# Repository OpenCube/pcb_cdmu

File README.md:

OpenCube CDMU
=============

The OpenCube Command and Data Management Unit (CDMU) is an embedded Linux computer. It coordinates the various functions of the spacecraft. In particular, it peforms the following tasks:

 * Telemetry pre-processing and encoding
 * Telecommand decoding
 * Communication session management
 * Resource allocation
 * Fault mitigation

In its current version, it consists of a BeagleBone Black board mounted on a custom circuit board with CAN bus transceivers. In the future, the board will also include a latch-up protection circuit, external memory (FRAM) and an external watchdog circuit. Eventually, the BeagleBone will be replaced with an AM3359 processor and its support components.

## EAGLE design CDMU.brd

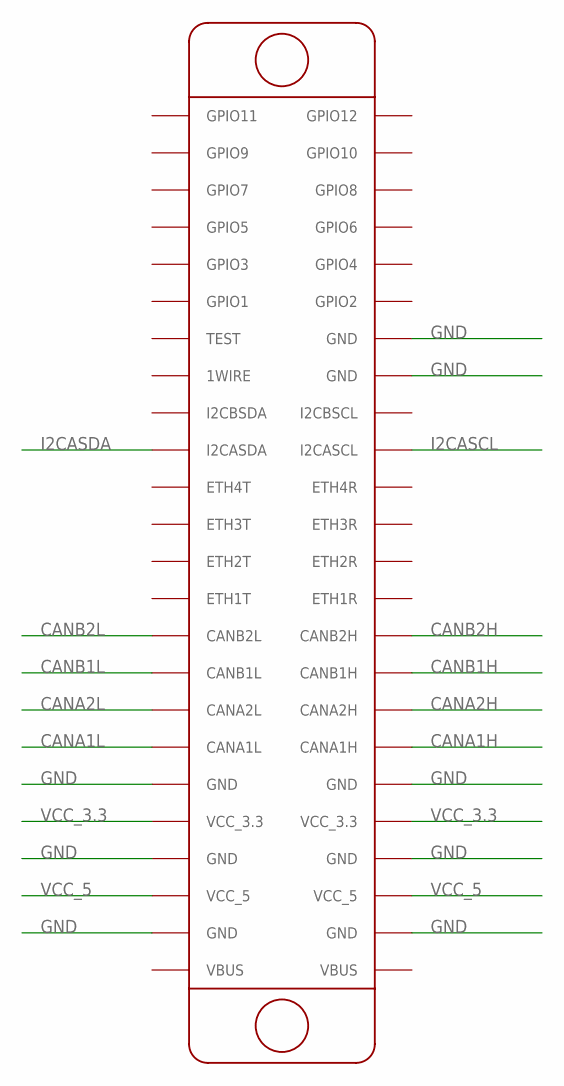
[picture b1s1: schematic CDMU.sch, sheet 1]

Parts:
U$1: CUBESAT_PCB

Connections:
CANA1H: U$1.CANA1H; also elsewhere on the board
CANA1L: U$1.CANA1L; also elsewhere on the board
CANA2H: U$1.CANA2H; also elsewhere on the board
CANA2L: U$1.CANA2L; also elsewhere on the board
CANB1H: U$1.CANB1H; also elsewhere on the board
CANB1L: U$1.CANB1L; also elsewhere on the board
CANB2H: U$1.CANB2H; also elsewhere on the board
CANB2L: U$1.CANB2L; also elsewhere on the board
GND: U$1.GND@5 (GND), U$1.GND@6 (GND), U$1.GND@7 (GND), U$1.GND@8 (GND), U$1.GND@9 (GND), U$1.GND@10 (GND), U$1.GND@11 (GND), U$1.GND@12 (GND); also elsewhere on the board
I2CASCL: U$1.I2CASCL; also elsewhere on the board
I2CASDA: U$1.I2CASDA; also elsewhere on the board
VCC_3.3: U$1.VCC_3.3@1 (VCC_3.3), U$1.VCC_3.3@2 (VCC_3.3); also elsewhere on the board
VCC_5: U$1.VCC_5@1 (VCC_5), U$1.VCC_5@2 (VCC_5); also elsewhere on the board

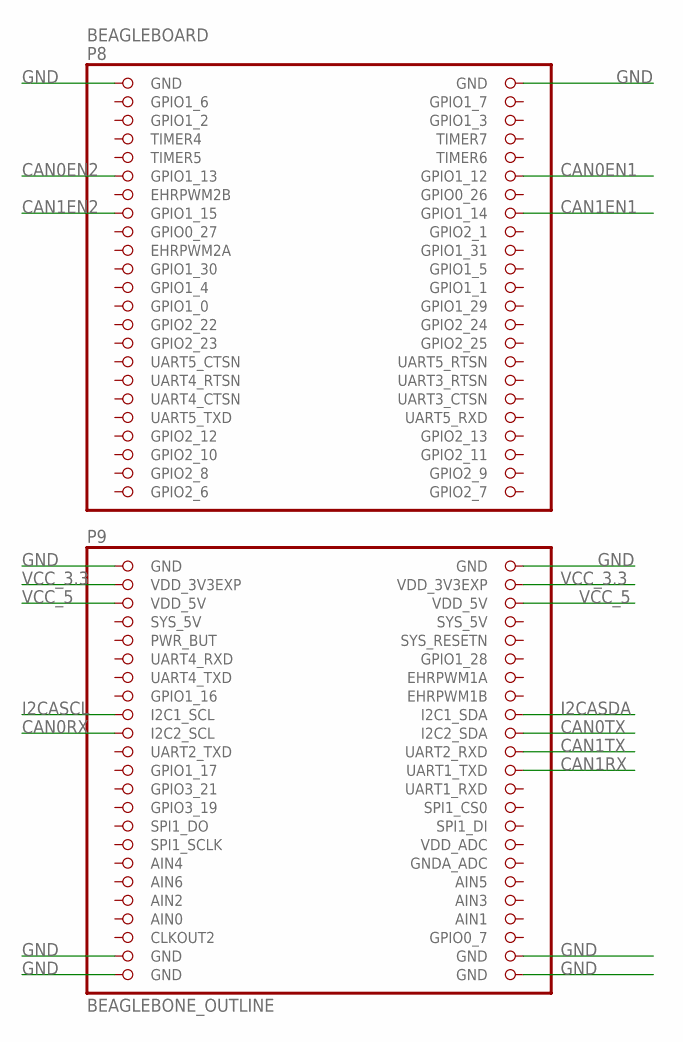
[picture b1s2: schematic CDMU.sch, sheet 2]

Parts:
BEAGLEBOARD: BEAGLEBONE_OUTLINE; BEAGLEBONE_SHIELD

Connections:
AIN0: BEAGLEBOARD.85 (AIN0)
CAN0EN1: BEAGLEBOARD.12 (GPIO1_12); also elsewhere on the board
CAN0EN2: BEAGLEBOARD.11 (GPIO1_13); also elsewhere on the board
CAN0RX: BEAGLEBOARD.65 (I2C2_SCL); also elsewhere on the board
CAN0TX: BEAGLEBOARD.66 (I2C2_SDA); also elsewhere on the board
CAN1EN1: BEAGLEBOARD.16 (GPIO1_14); also elsewhere on the board
CAN1EN2: BEAGLEBOARD.15 (GPIO1_15); also elsewhere on the board
CAN1RX: BEAGLEBOARD.70 (UART1_TXD); also elsewhere on the board
CAN1TX: BEAGLEBOARD.68 (UART2_RXD); also elsewhere on the board
GND: BEAGLEBOARD.1 (GND), BEAGLEBOARD.2 (GND), BEAGLEBOARD.47 (GND), BEAGLEBOARD.48 (GND), BEAGLEBOARD.89 (GND), BEAGLEBOARD.90 (GND), BEAGLEBOARD.91 (GND), BEAGLEBOARD.92 (GND); also elsewhere on the board
I2CASCL: BEAGLEBOARD.63 (I2C1_SCL); also elsewhere on the board
I2CASDA: BEAGLEBOARD.64 (I2C1_SDA); also elsewhere on the board
SYS_5V: BEAGLEBOARD.53 (SYS_5V)
VCC_3.3: BEAGLEBOARD.49 (VDD_3V3EXP), BEAGLEBOARD.50 (VDD_3V3EXP); also elsewhere on the board
VCC_5: BEAGLEBOARD.51 (VDD_5V), BEAGLEBOARD.52 (VDD_5V); also elsewhere on the board

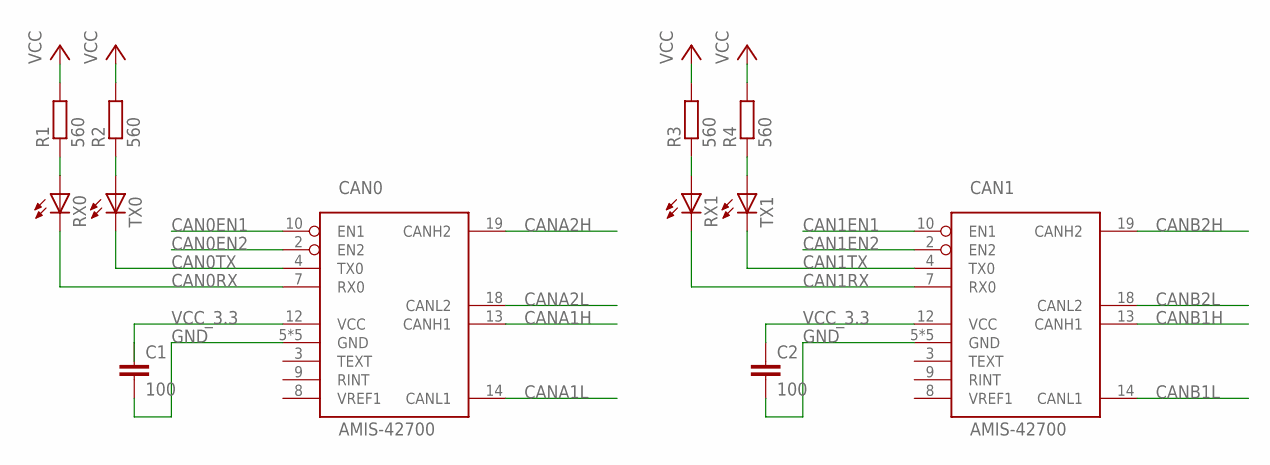
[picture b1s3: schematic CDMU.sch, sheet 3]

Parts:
C1, C2: 100; C0805
CAN0, CAN1: AMIS-42700; SOIC20
R1, R2, R3, R4: 560; R0805
RX0, RX1: LED3MM
TX0, TX1: LED3MM

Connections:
CAN0EN1: CAN0.10 (EN1); also elsewhere on the board
CAN0EN2: CAN0.2 (EN2); also elsewhere on the board
CAN0RX: CAN0.7 (RX0), RX0.K (C); also elsewhere on the board
CAN0TX: CAN0.4 (TX0), TX0.K (C); also elsewhere on the board
CAN1EN1: CAN1.10 (EN1); also elsewhere on the board
CAN1EN2: CAN1.2 (EN2); also elsewhere on the board
CAN1RX: CAN1.7 (RX0), RX1.K (C); also elsewhere on the board
CAN1TX: CAN1.4 (TX0), TX1.K (C); also elsewhere on the board
CANA1H: CAN0.13 (CANH1); also elsewhere on the board
CANA1L: CAN0.14 (CANL1); also elsewhere on the board
CANA2H: CAN0.19 (CANH2); also elsewhere on the board
CANA2L: CAN0.18 (CANL2); also elsewhere on the board
CANB1H: CAN1.13 (CANH1); also elsewhere on the board
CANB1L: CAN1.14 (CANL1); also elsewhere on the board
CANB2H: CAN1.19 (CANH2); also elsewhere on the board
CANB2L: CAN1.18 (CANL2); also elsewhere on the board
GND: C1.2, C2.2, CAN0.5 (GND), CAN0.6 (GND), CAN0.15 (GND), CAN0.16 (GND), CAN0.17 (GND), CAN1.5 (GND), CAN1.6 (GND), CAN1.15 (GND), CAN1.16 (GND), CAN1.17 (GND); also elsewhere on the board
unnamed: R1.1, RX0.A
unnamed: R2.1, TX0.A
unnamed: R3.1, RX1.A
unnamed: R4.1, TX1.A
VCC_3.3: C1.1, C2.1, CAN0.12 (VCC), CAN1.12 (VCC), R1.2, R2.2, R3.2, R4.2; also elsewhere on the board

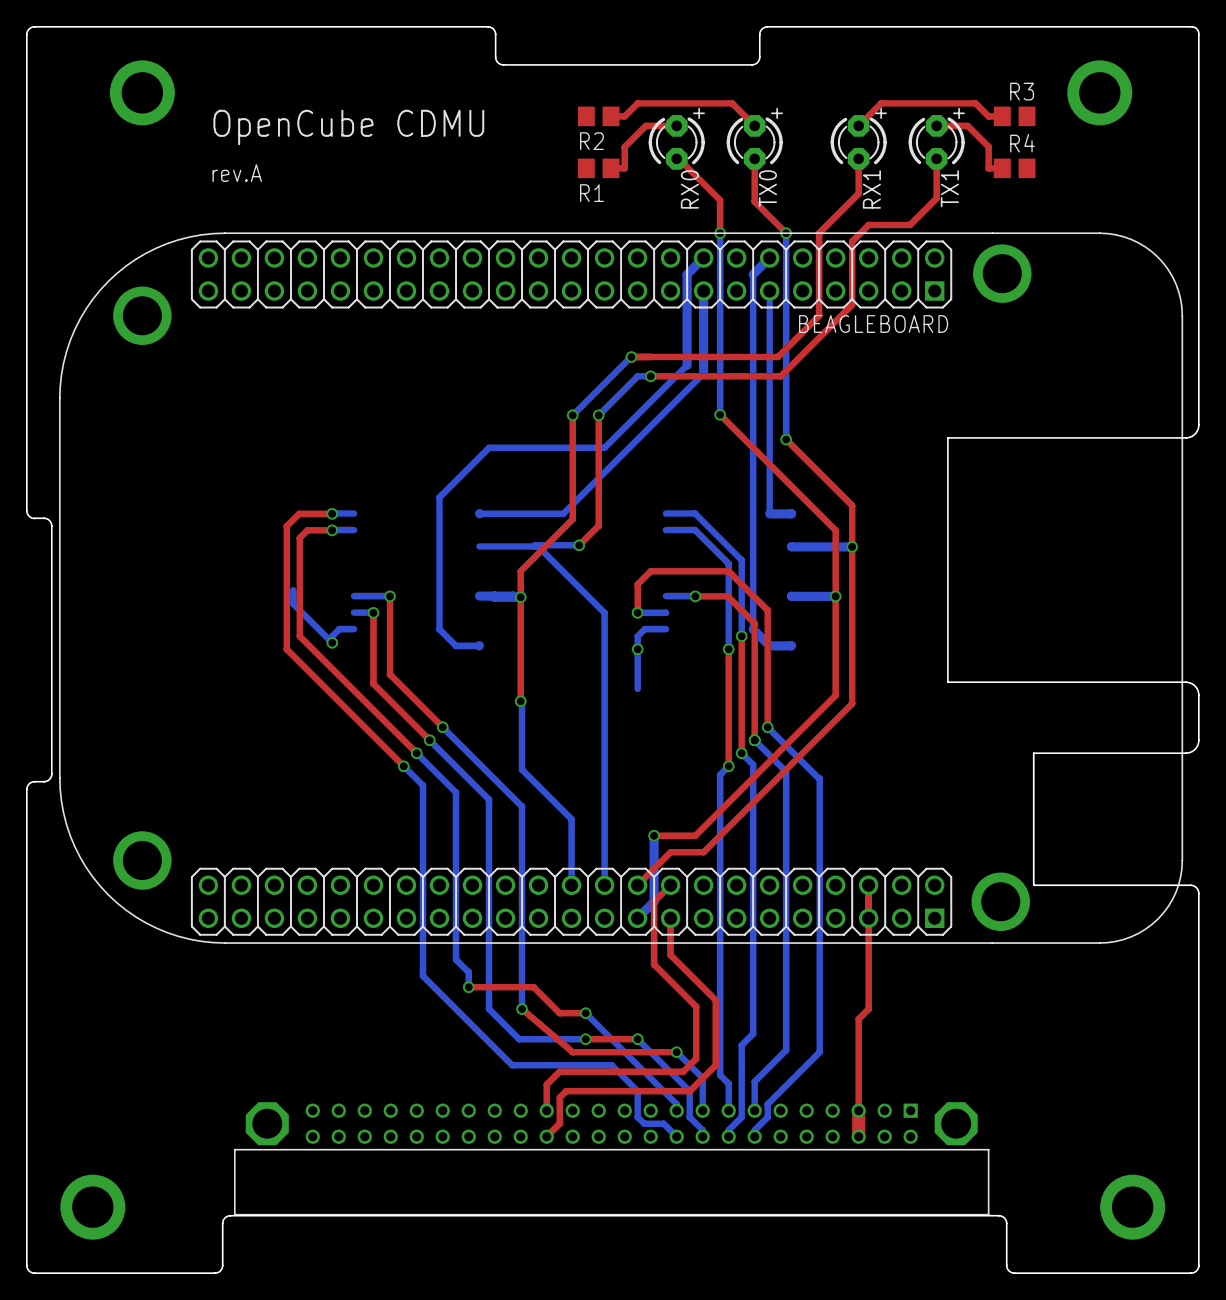
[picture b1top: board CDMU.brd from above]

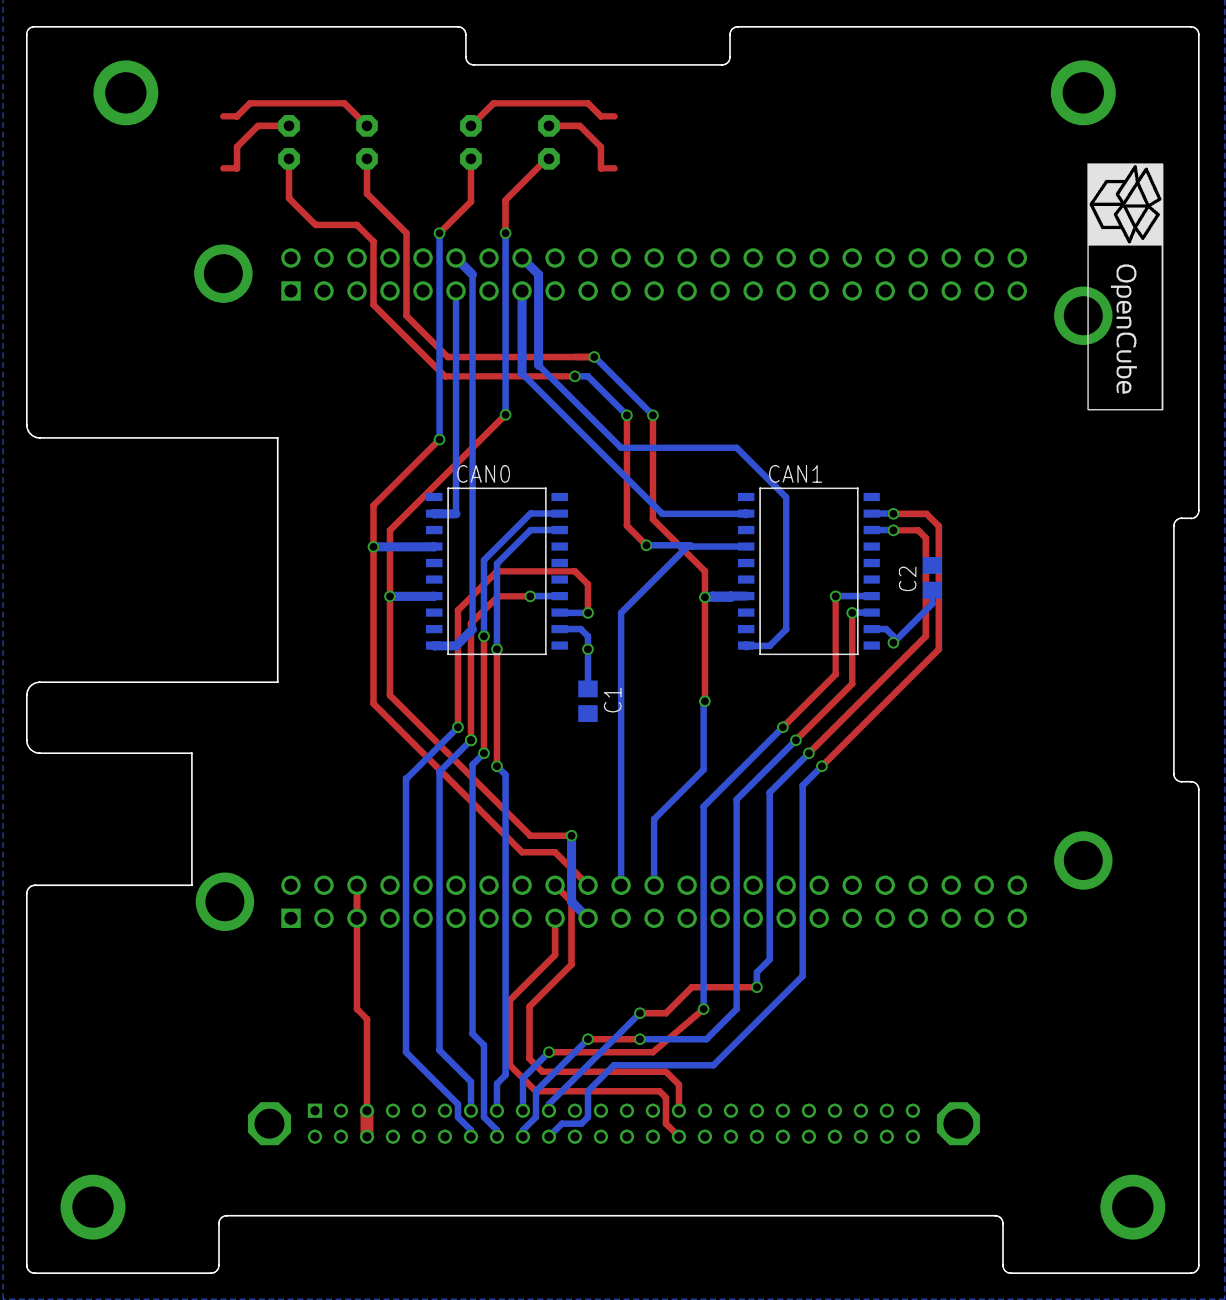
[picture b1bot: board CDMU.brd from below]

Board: 4 copper layers, 90.2 x 95.9 mm, 14 parts (4 on the bottom side), 25 nets.
